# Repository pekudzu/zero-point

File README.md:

# zero-point

a diodeless 32-key ergo board, driven by an RP2040-zero.

support for a trackpoint, circuit shamelessly stolen from the buzzard

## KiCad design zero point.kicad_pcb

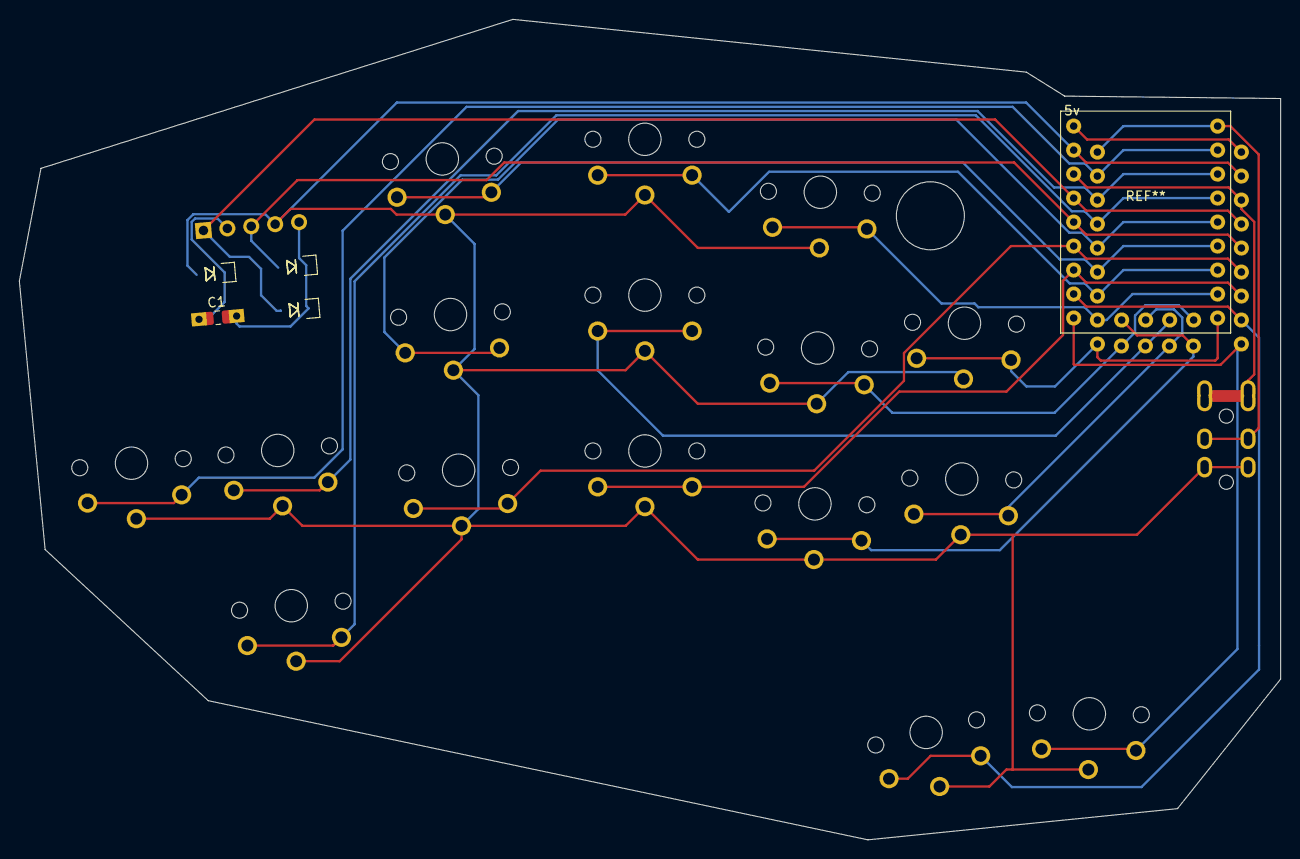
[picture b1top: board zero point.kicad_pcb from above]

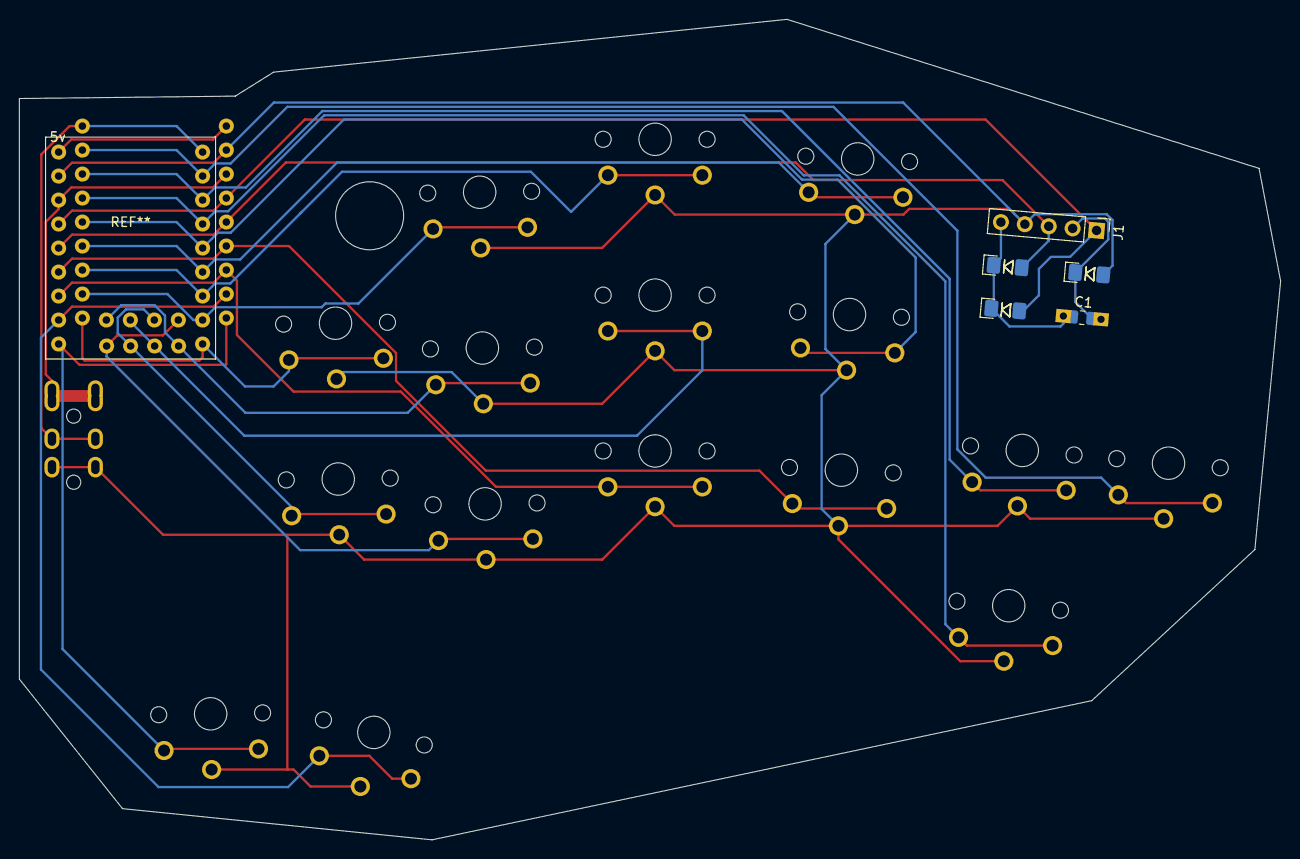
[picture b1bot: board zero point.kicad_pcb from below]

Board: 2 copper layers, 133.5 x 86.9 mm, 21 parts (5 on the bottom side), 5 nets.

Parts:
C1: 2.2uF; C_THT_SMD_0805_HandSolder_Reversable
J1: TrackPoint; PinHeader_1x05_P2.54mm_Vertical
R1, R2: 4.7kΩ; D_1206_handsolder
R3: 100kΩ; D_1206_handsolder
S1, S2, S3, S4, S5, S6, S7, S8, S9, S10, S11, S12, S13, S14, S15, S16: PG1350

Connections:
GND: J1.4, R3.2, S1.2, S2.2, S3.2, S4.2, S5.2, S6.2, S7.2, S8.2, S9.2, S10.2, S11.2, S12.2, S13.2, S14.2, S15.2, S16.2
unnamed: C1.2, J1.2, R3.1
TP_CLK: J1.3, R1.2
TP_DATA: J1.1, R2.2
VCC: C1.1, J1.5, R1.1, R2.1
